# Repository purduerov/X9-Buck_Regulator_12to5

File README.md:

# X9-PCB-Buck_Regulator_12to5
This printed circuit board utilizes the LM2678 integrated circuit to efficiently convert 12V to 5V.  http://www.ti.com/lit/ds/symlink/lm2678.pdf

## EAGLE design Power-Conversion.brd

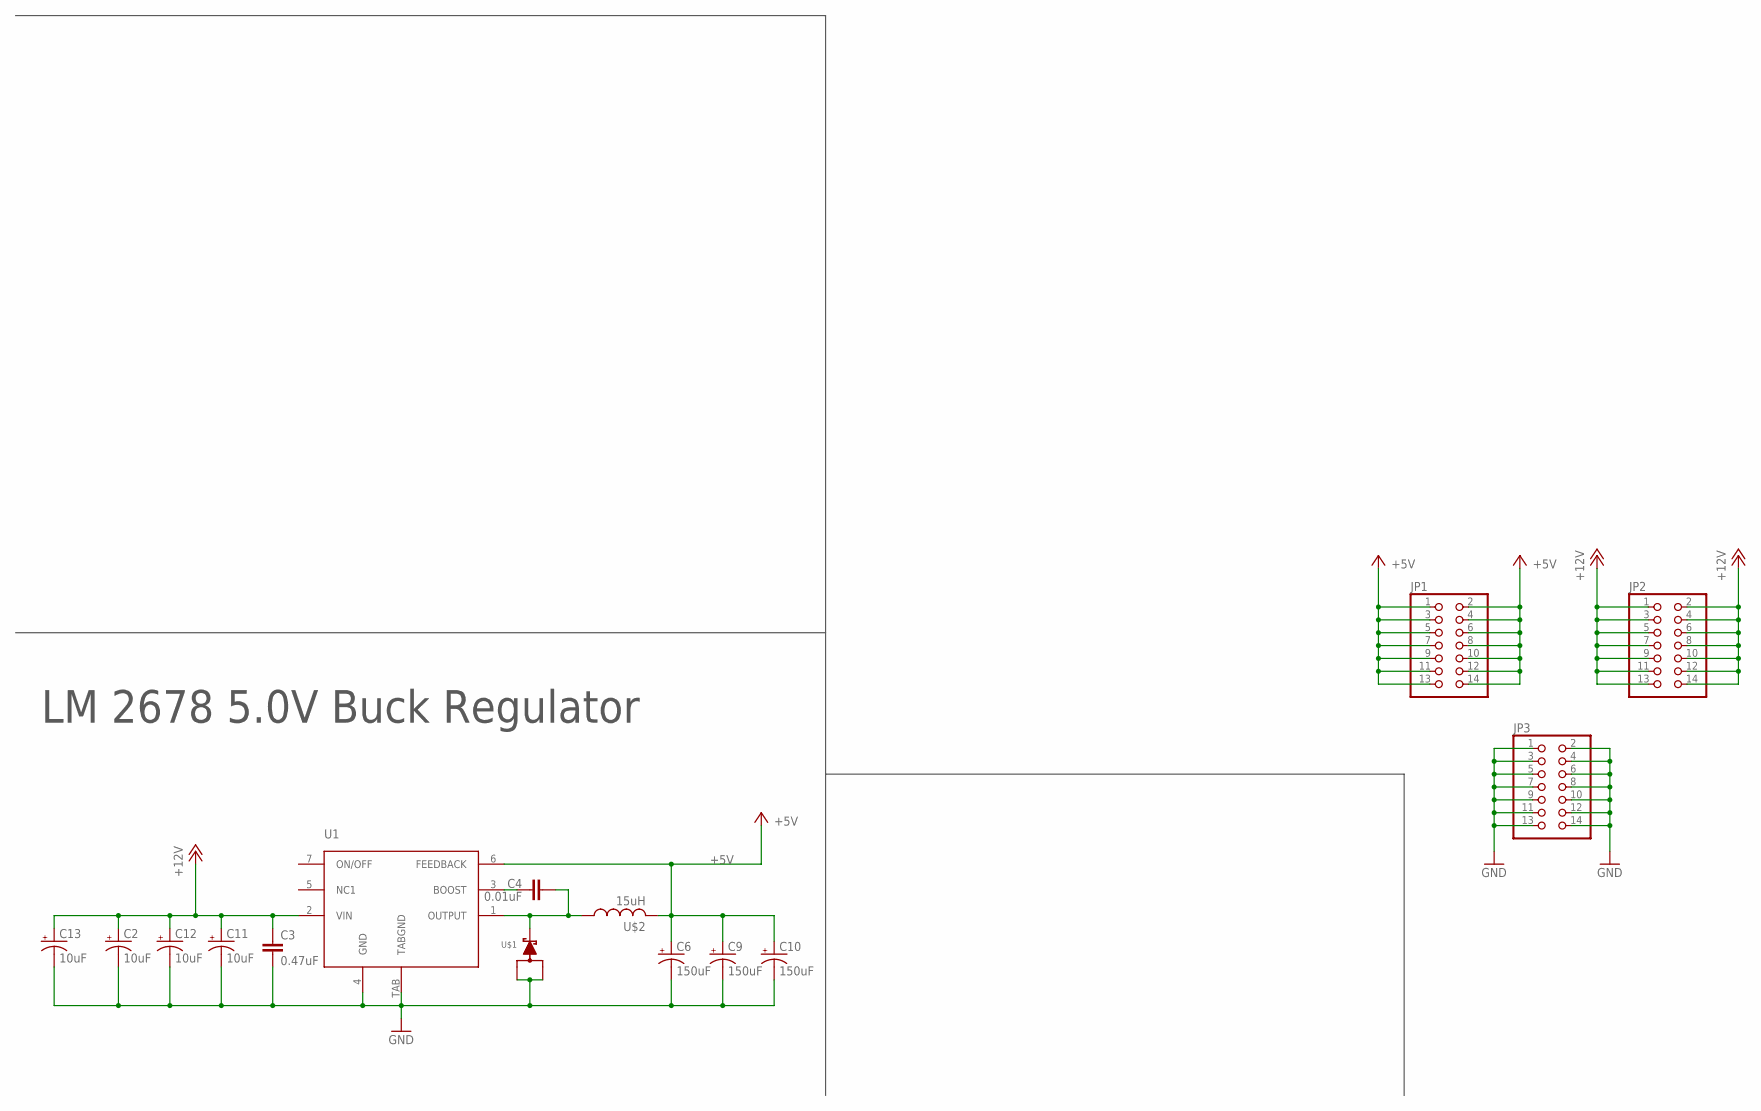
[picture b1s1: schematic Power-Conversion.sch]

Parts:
C2, C11, C12, C13: 10uF; CTAN(7.30_4.30MM)
C3: 0.47uF; 0805
C4: 0.01uF; 0603-CAP
C6, C9, C10: 150uF; CTAN(7.30_4.30MM)
JP1, JP2, JP3: PINHD-2X7; 2X07
U1: LM2678
U$1: SWITCHMODE_SCHOTTKY; DPAK-3
U$2: 15uH; HCMA1305

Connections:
+5V: C6.+, C9.+, C10.+, JP1.1, JP1.2, JP1.3, JP1.4, JP1.5, JP1.6, JP1.7, JP1.8, JP1.9, JP1.10, JP1.11, JP1.12, JP1.13, JP1.14, U1.6 (FEEDBACK), U$2.P$2 (2)
+12V: C2.+, C3.1, C11.+, C12.+, C13.+, JP2.1, JP2.2, JP2.3, JP2.4, JP2.5, JP2.6, JP2.7, JP2.8, JP2.9, JP2.10, JP2.11, JP2.12, JP2.13, JP2.14, U1.2 (VIN)
GND: C2.-, C3.2, C6.-, C9.-, C10.-, C11.-, C12.-, C13.-, JP3.1, JP3.2, JP3.3, JP3.4, JP3.5, JP3.6, JP3.7, JP3.8, JP3.9, JP3.10, JP3.11, JP3.12, JP3.13, JP3.14, U1.4 (GND), U1.TAB (TABGND), U$1.P$1, U$1.P$3
unnamed: C4.1, U1.3 (BOOST)
unnamed: C4.2, U1.1 (OUTPUT), U$1.P$4, U$2.P$1 (1)

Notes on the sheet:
LM 2678 5.0V Buck Regulator

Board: 2 copper layers, 15 parts (4 on the bottom side), 5 nets, no tracks yet.

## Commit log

2016-11-02 OutputJob

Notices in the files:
parts and their libraries:
SparkFun-Passives: Licensing: Creative Commons ShareAlike 4.0 International - https://creativecommons.org/licenses/by-sa/4.0
